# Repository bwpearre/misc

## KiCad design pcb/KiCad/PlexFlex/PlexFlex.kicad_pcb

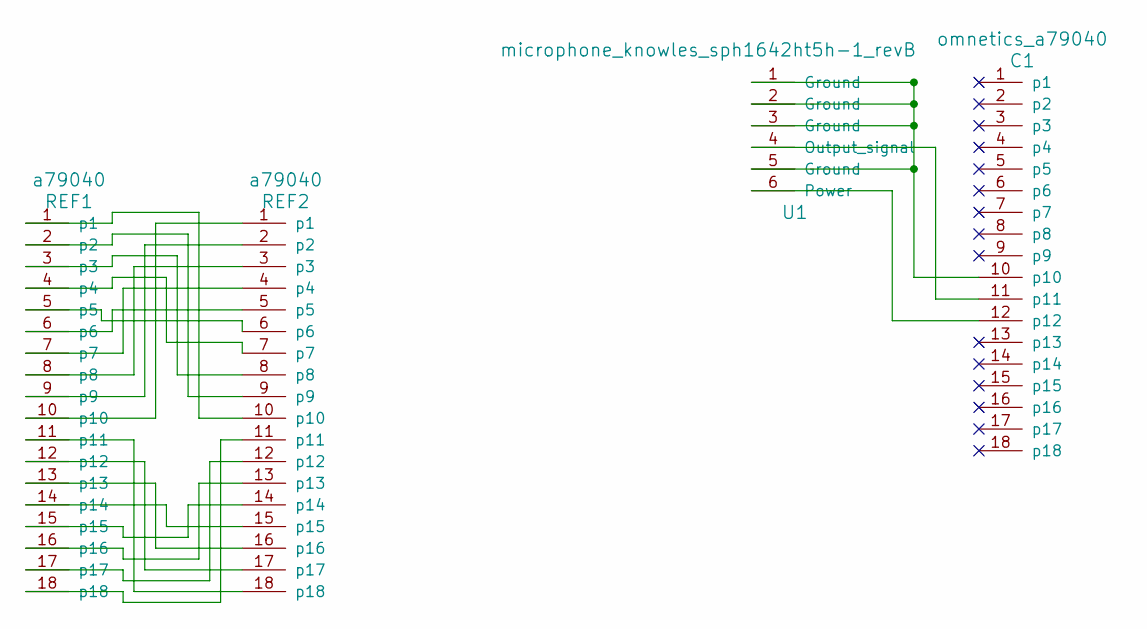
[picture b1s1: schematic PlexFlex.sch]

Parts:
C1: omnetics_a79040; a79040
REF1, REF2: a79040
U1: microphone_knowles_sph1642ht5h-1_revB

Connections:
unnamed: C1.10 (p10), U1.1 (Ground), U1.2 (Ground), U1.3 (Ground), U1.5 (Ground)
unnamed: C1.11 (p11), U1.4 (Output_signal)
unnamed: C1.12 (p12), U1.6 (Power)
unnamed: REF1.1 (p1), REF2.10 (p10)
unnamed: REF1.2 (p2), REF2.9 (p9)
unnamed: REF1.3 (p3), REF2.8 (p8)
unnamed: REF1.4 (p4), REF2.7 (p7)
unnamed: REF1.5 (p5), REF2.6 (p6)
unnamed: REF1.6 (p6), REF2.5 (p5)
unnamed: REF1.7 (p7), REF2.4 (p4)
unnamed: REF1.8 (p8), REF2.3 (p3)
unnamed: REF1.9 (p9), REF2.2 (p2)
unnamed: REF1.10 (p10), REF2.1 (p1)
unnamed: REF1.11 (p11), REF2.18 (p18)
unnamed: REF1.12 (p12), REF2.17 (p17)
unnamed: REF1.13 (p13), REF2.16 (p16)
unnamed: REF1.14 (p14), REF2.15 (p15)
unnamed: REF1.15 (p15), REF2.14 (p14)
unnamed: REF1.16 (p16), REF2.13 (p13)
unnamed: REF1.17 (p17), REF2.12 (p12)
unnamed: REF1.18 (p18), REF2.11 (p11)

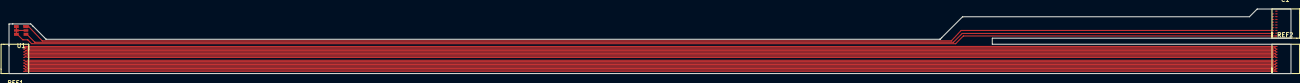
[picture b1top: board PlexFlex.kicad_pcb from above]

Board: 2 copper layers, 294.8 x 14.8 mm, 4 parts (0 on the bottom side), 21 nets.

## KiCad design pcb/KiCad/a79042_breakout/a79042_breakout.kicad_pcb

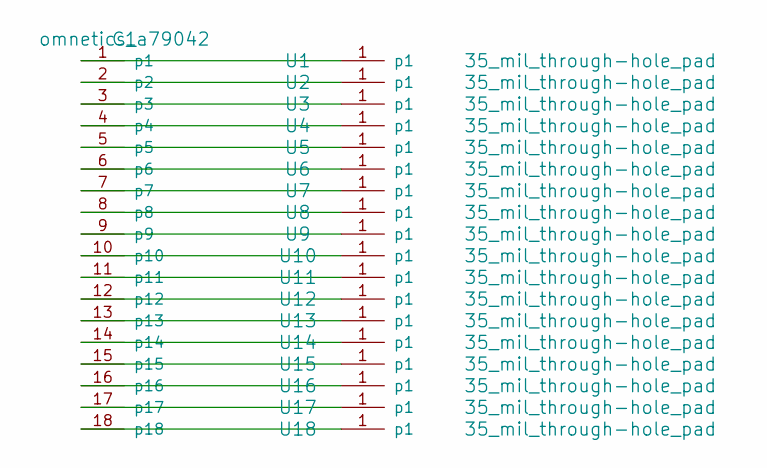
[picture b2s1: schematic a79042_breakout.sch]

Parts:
C1: omnetics_a79042; a79042
U1, U2, U3, U4, U5, U6, U7, U8, U9, U10, U11, U12, U13, U14, U15, U16, U17, U18: 35_mil_through-hole_pad; 35_mil_though-hole_pad

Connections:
unnamed: C1.1 (p1), U1.1
unnamed: C1.2 (p2), U2.1
unnamed: C1.3 (p3), U3.1
unnamed: C1.4 (p4), U4.1
unnamed: C1.5 (p5), U5.1
unnamed: C1.6 (p6), U6.1
unnamed: C1.7 (p7), U7.1
unnamed: C1.8 (p8), U8.1
unnamed: C1.9 (p9), U9.1
unnamed: C1.10 (p10), U10.1
unnamed: C1.11 (p11), U11.1
unnamed: C1.12 (p12), U12.1
unnamed: C1.13 (p13), U13.1
unnamed: C1.14 (p14), U14.1
unnamed: C1.15 (p15), U15.1
unnamed: C1.16 (p16), U16.1
unnamed: C1.17 (p17), U17.1
unnamed: C1.18 (p18), U18.1

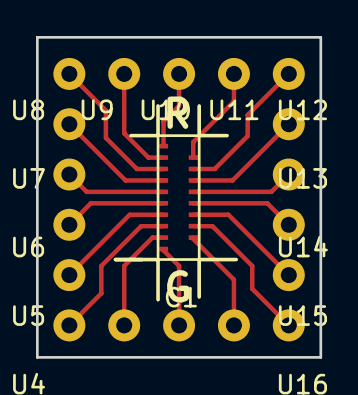
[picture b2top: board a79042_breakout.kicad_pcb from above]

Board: 2 copper layers, 15.7 x 17.8 mm, 19 parts (0 on the bottom side), 18 nets.

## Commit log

2016-07-18 KiCad designs for my Rev 0 live stimulator:
    - 18-channel flex cable (Omnetics to Omnetics)
    - 18-channel PCB breakout for 16-ch+2 Omnetics a79042
2016-07-18 Reorganise. Delete autosave files.
    Need to update library locations, etc, in project files.
2016-07-19 Add silkscreen placement guide.
2016-07-20 Updated library locations, etc.
    a79040_breakout: submitted to 4pcb.com for production.
    PlexFlex: Still working.
2016-08-03 Add microphone: knowles_sph1642ht5h-1_revB - Footprint - Schematic - Add to flex cable design
2016-08-04 Reshape edge cuts. Submitted this version for production.
